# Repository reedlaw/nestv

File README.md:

# nestv

FPGA CRT console research and implementation, beginning with a native-rate
NTSC Y/C encoder path for NESTang on the Tang Primer 25K.

The engineering plan and milestone definitions live in [PROJECT.md](PROJECT.md).

## Prerequisites

- GNU Make
- `curl` and `sha256sum`
- Verilator 5 or newer
- Python 3 with NumPy
- Gowin EDA 1.9.12.03 for FPGA synthesis (not required for tests)

## Quick start

```sh
make bootstrap
make check
```

`make bootstrap` downloads the exact pinned `yc_out.sv` revision and verifies
its SHA-256 digest. Generated and downloaded files are kept under `build/`.

Useful targets:

```sh
make lint             # Verilator lint
make test             # standalone yc_out simulation
make wave             # generate an FST waveform for GTKWave
make wave-open        # generate and open the waveform
make validate-m1      # export Y/C, decode frames, compare 6/8-bit DACs
make synth-primer25k  # reproducible Gowin entry point
make clean
```

If `Gowin_V1.9.12.03_linux.tar.gz` is in the repository root, unpack its
`IDE/` directory beneath `.tools/gowin/1.9.12.03/`. The synthesis wrapper
detects that location automatically.

Upstream revisions and licensing are recorded in [THIRD_PARTY.md](THIRD_PARTY.md).

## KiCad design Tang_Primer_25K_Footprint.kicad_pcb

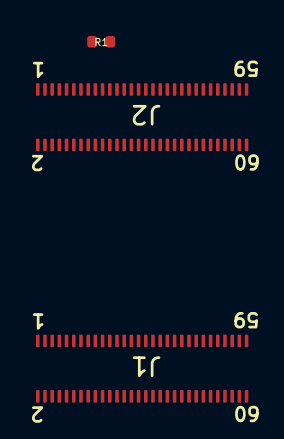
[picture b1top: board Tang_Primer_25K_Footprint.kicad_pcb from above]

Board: 2 copper layers, 3 parts (0 on the bottom side), 9 nets, no tracks yet.

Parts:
J1, J2: DF40C-60DS-0.4V(51); BTB-DF40C-60DS-0.4V(51)#
R1: 5.1K; R_0402

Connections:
+5V: J2.52, J2.54, J2.56, J2.58, J2.60
/C1_JTAG_TCK: J2.21, R1.2
/VCCIO0/1: J1.24, J1.26
/VCCIO2/3: J2.2, J2.4
/VCCIO6/7: J1.29, J1.31
/VDD_1V8: J2.38, J2.40
/VDD_2V5: J2.42, J2.44
/VDD_3V3: J2.46, J2.48, J2.50
GND: J1.1, J1.2, J1.15, J1.27, J1.28, J1.45, J1.50, J1.59, J1.60, J2.1, J2.19, J2.29, J2.35, J2.41, J2.47, J2.53, J2.59, R1.1
